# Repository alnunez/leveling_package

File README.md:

## Directory structure
* hardware: Kicad 5.1.5
* software: Mongoose OS 2.19.1

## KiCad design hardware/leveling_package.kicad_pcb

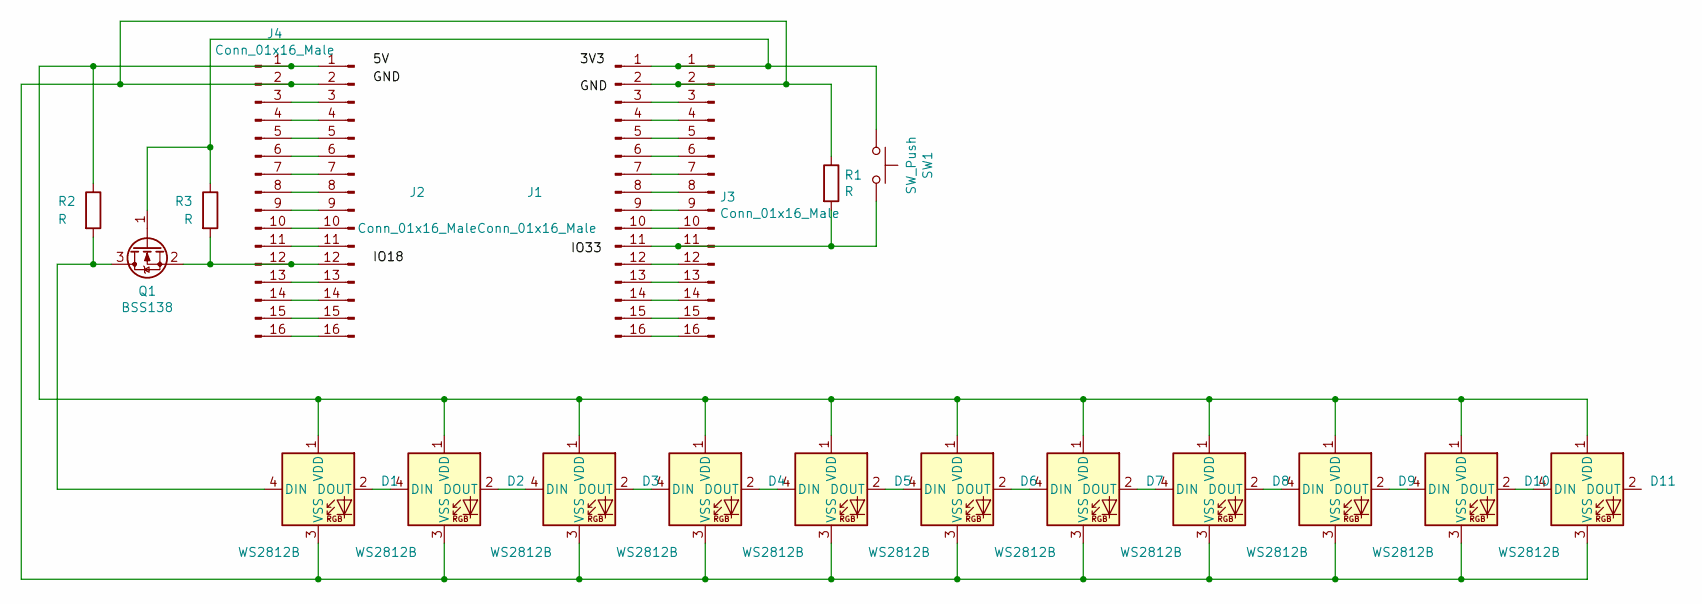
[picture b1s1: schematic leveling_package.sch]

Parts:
D1, D2, D3, D4, D5, D6, D7, D8, D9, D10, D11: WS2812B; LED_WS2812B_PLCC4_5.0x5.0mm_P3.2mm
J1, J2, J3, J4: Conn_01x16_Male; PinHeader_1x16_P2.54mm_Vertical
Q1: BSS138; SOT-23
R1, R2, R3: R; R_0805_2012Metric_Pad1.15x1.40mm_HandSolder
SW1: SW_Push; SW_PUSH_6mm

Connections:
unnamed: D1.1 (VDD), D2.1 (VDD), D3.1 (VDD), D4.1 (VDD), D5.1 (VDD), D6.1 (VDD), D7.1 (VDD), D8.1 (VDD), D9.1 (VDD), D10.1 (VDD), D11.1 (VDD), J2.1, J4.1, R2.1
unnamed: D1.2 (DOUT), D2.4 (DIN)
unnamed: D1.3 (VSS), D2.3 (VSS), D3.3 (VSS), D4.3 (VSS), D5.3 (VSS), D6.3 (VSS), D7.3 (VSS), D8.3 (VSS), D9.3 (VSS), D10.3 (VSS), D11.3 (VSS), J1.2, J2.2, J3.2, J4.2, R1.1
unnamed: D1.4 (DIN), Q1.3 (D), R2.2
unnamed: D2.2 (DOUT), D3.4 (DIN)
unnamed: D3.2 (DOUT), D4.4 (DIN)
unnamed: D4.2 (DOUT), D5.4 (DIN)
unnamed: D5.2 (DOUT), D6.4 (DIN)
unnamed: D6.2 (DOUT), D7.4 (DIN)
unnamed: D7.2 (DOUT), D8.4 (DIN)
unnamed: D8.2 (DOUT), D9.4 (DIN)
unnamed: D10.2 (DOUT), D11.4 (DIN)
unnamed: D9.2 (DOUT), D10.4 (DIN)
unnamed: J1.1, J3.1, Q1.1 (G), R3.1, SW1.1
unnamed: J1.3, J3.3
unnamed: J1.4, J3.4
unnamed: J1.5, J3.5
unnamed: J1.6, J3.6
unnamed: J1.7, J3.7
unnamed: J1.8, J3.8
unnamed: J1.9, J3.9
unnamed: J1.10, J3.10
unnamed: J1.11, J3.11, R1.2, SW1.2
unnamed: J1.12, J3.12
unnamed: J1.13, J3.13
unnamed: J1.14, J3.14
unnamed: J1.15, J3.15
unnamed: J1.16, J3.16
unnamed: J2.3, J4.3
unnamed: J2.4, J4.4
unnamed: J2.5, J4.5
unnamed: J2.6, J4.6
unnamed: J2.7, J4.7
unnamed: J2.8, J4.8
unnamed: J2.9, J4.9
unnamed: J2.10, J4.10
unnamed: J2.11, J4.11
unnamed: J2.12, J4.12, Q1.2 (S), R3.2
unnamed: J2.13, J4.13
unnamed: J2.14, J4.14
unnamed: J2.15, J4.15
unnamed: J2.16, J4.16

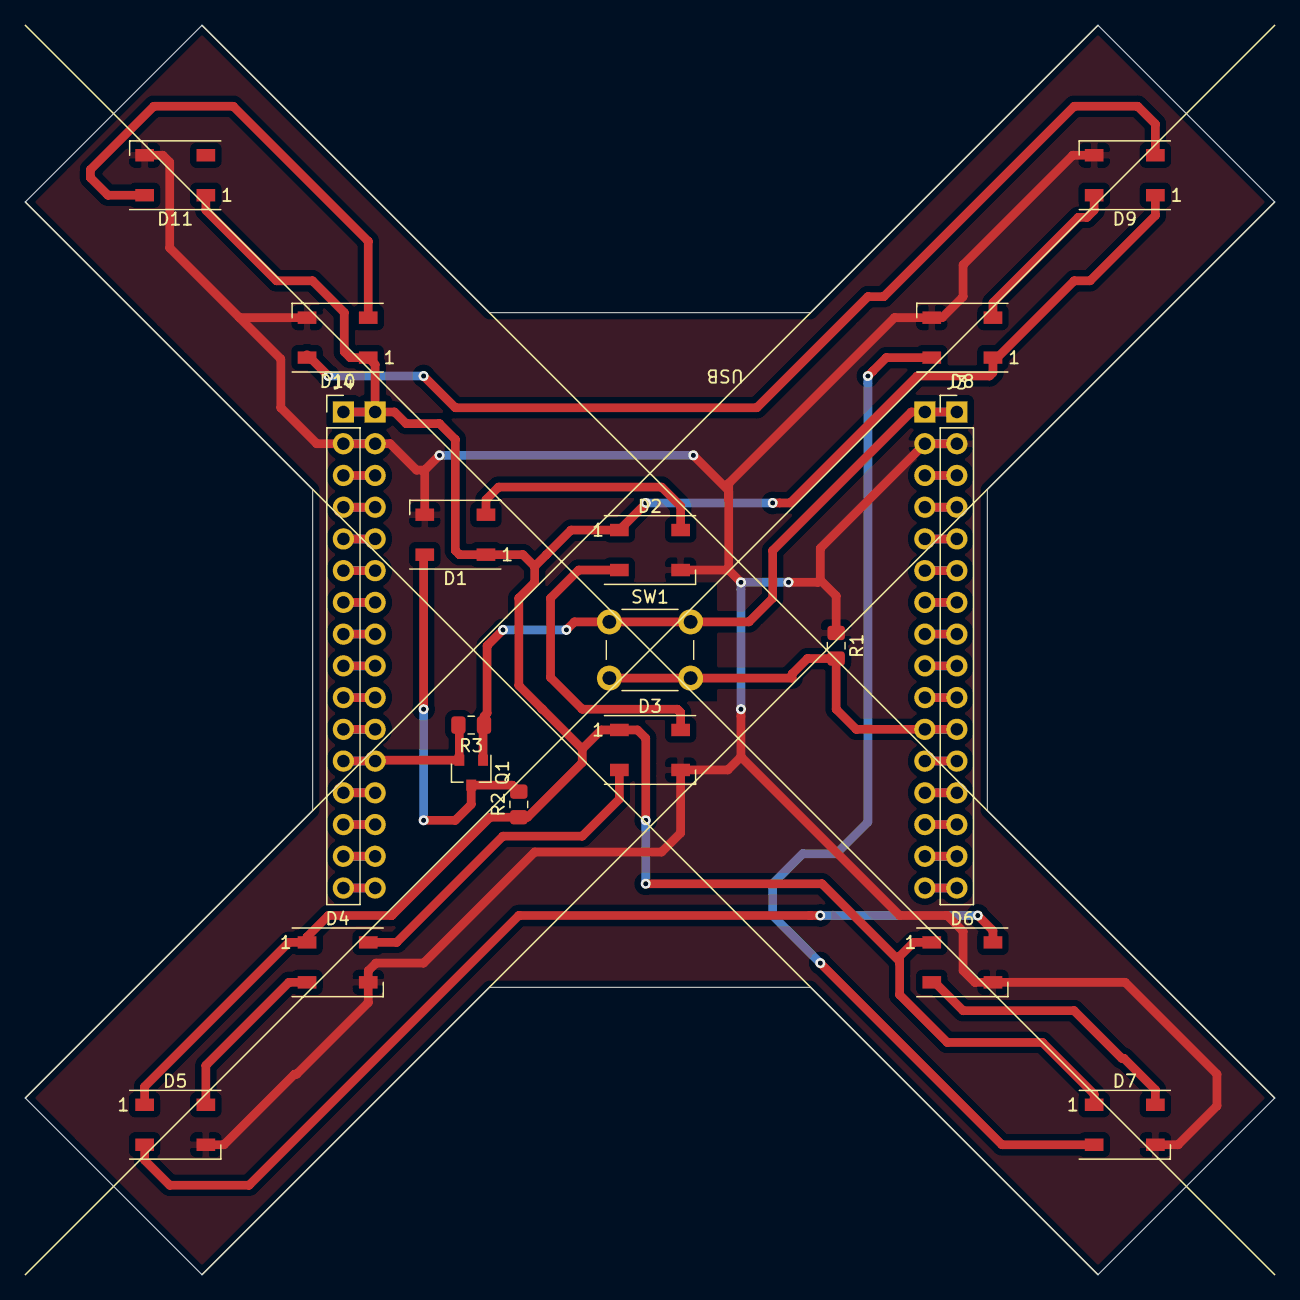
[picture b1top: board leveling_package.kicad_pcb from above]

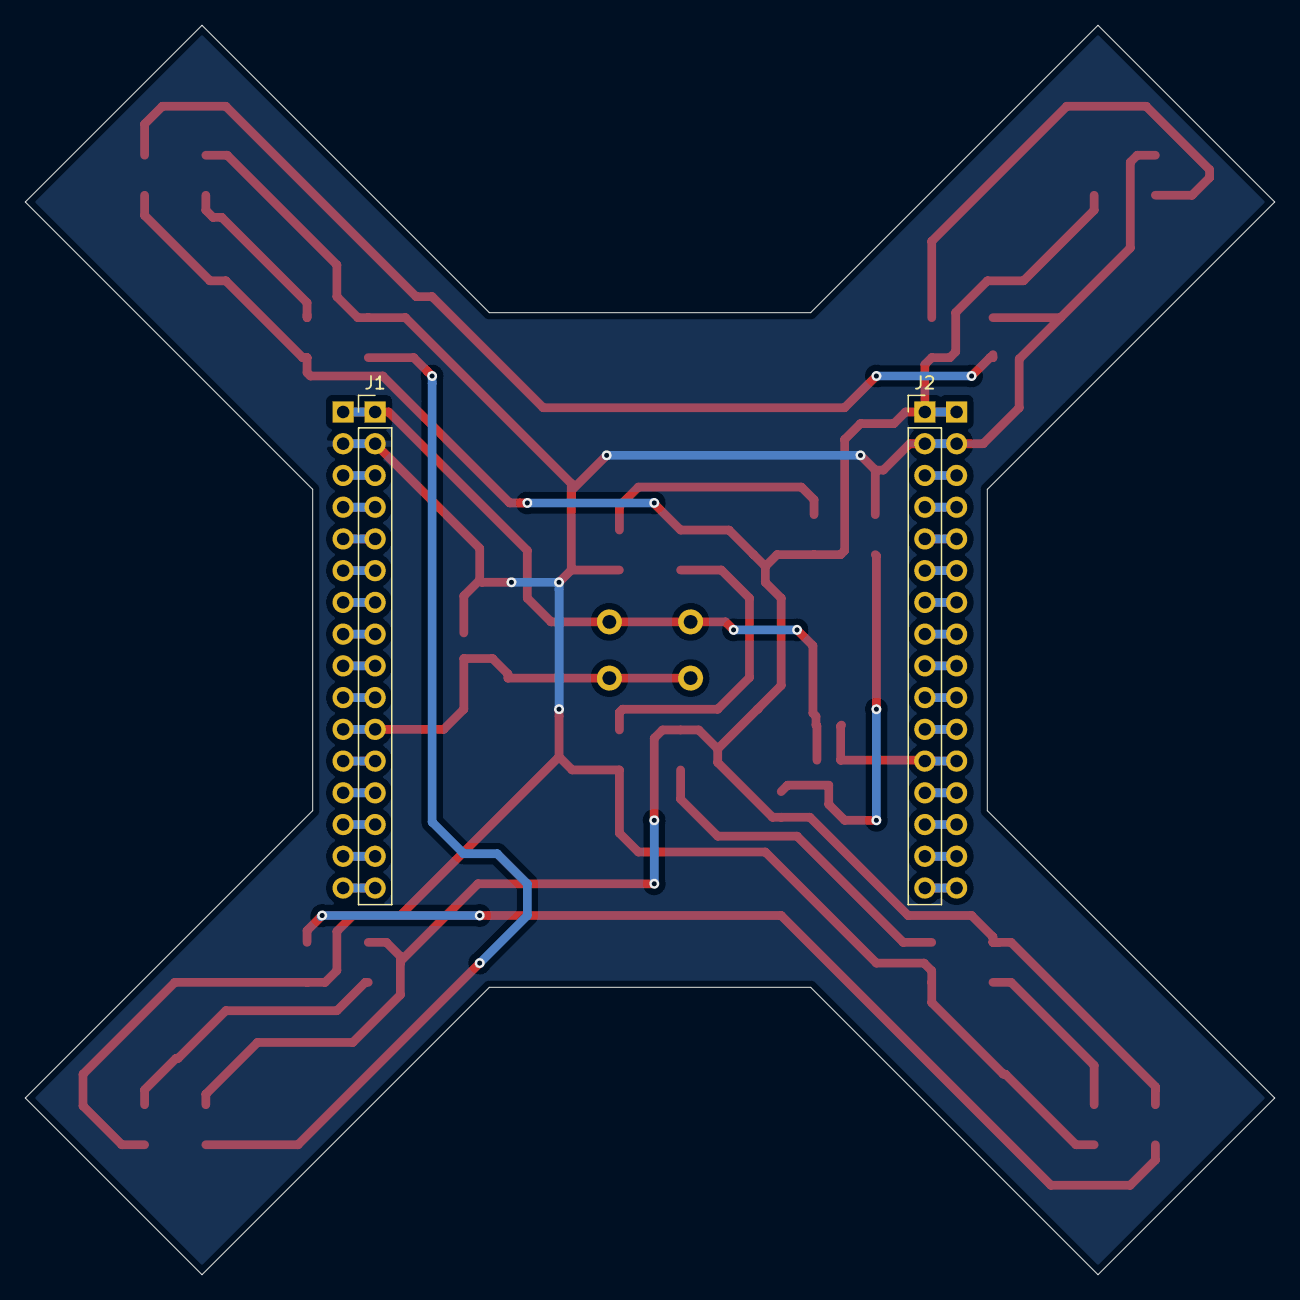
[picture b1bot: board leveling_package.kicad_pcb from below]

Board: 2 copper layers, 100.0 x 100.0 mm, 20 parts (2 on the bottom side), 42 nets.

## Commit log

2021-03-02 first leg
2021-03-02 2nd leg
2021-03-03 3rd leg
2021-03-03 4rd leg
2021-03-03 first leg with all leds
2021-03-03 all legs with leds
2021-03-04 reame hints
2021-03-04 firmware tests
2021-03-05 firmware tests neopix
2021-03-05 all traces routed
2021-03-05 legs a bit wider
2021-03-05 added proto solder pads
2021-03-05 minor corrections
2021-03-24 trig functions started
2021-03-24 z axis added to accel readings
2021-03-25 tests of change config via BLE
